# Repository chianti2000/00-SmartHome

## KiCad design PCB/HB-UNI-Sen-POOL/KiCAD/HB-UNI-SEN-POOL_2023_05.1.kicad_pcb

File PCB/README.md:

Dies ist eine Sammplung meiner Platinen für den Bereich HomeMatic, AskSinPP und usw.

## HB-UNI-TEST-PROG-BOARD 

Eine Platine zum Programmieren des ARDUINO PRO MINI und der AVR 328P-AU /1284P-AU sowie für den Frequenztest / Frequenzpairing des Arduino / AVR mit dem CC1101. 

</img>

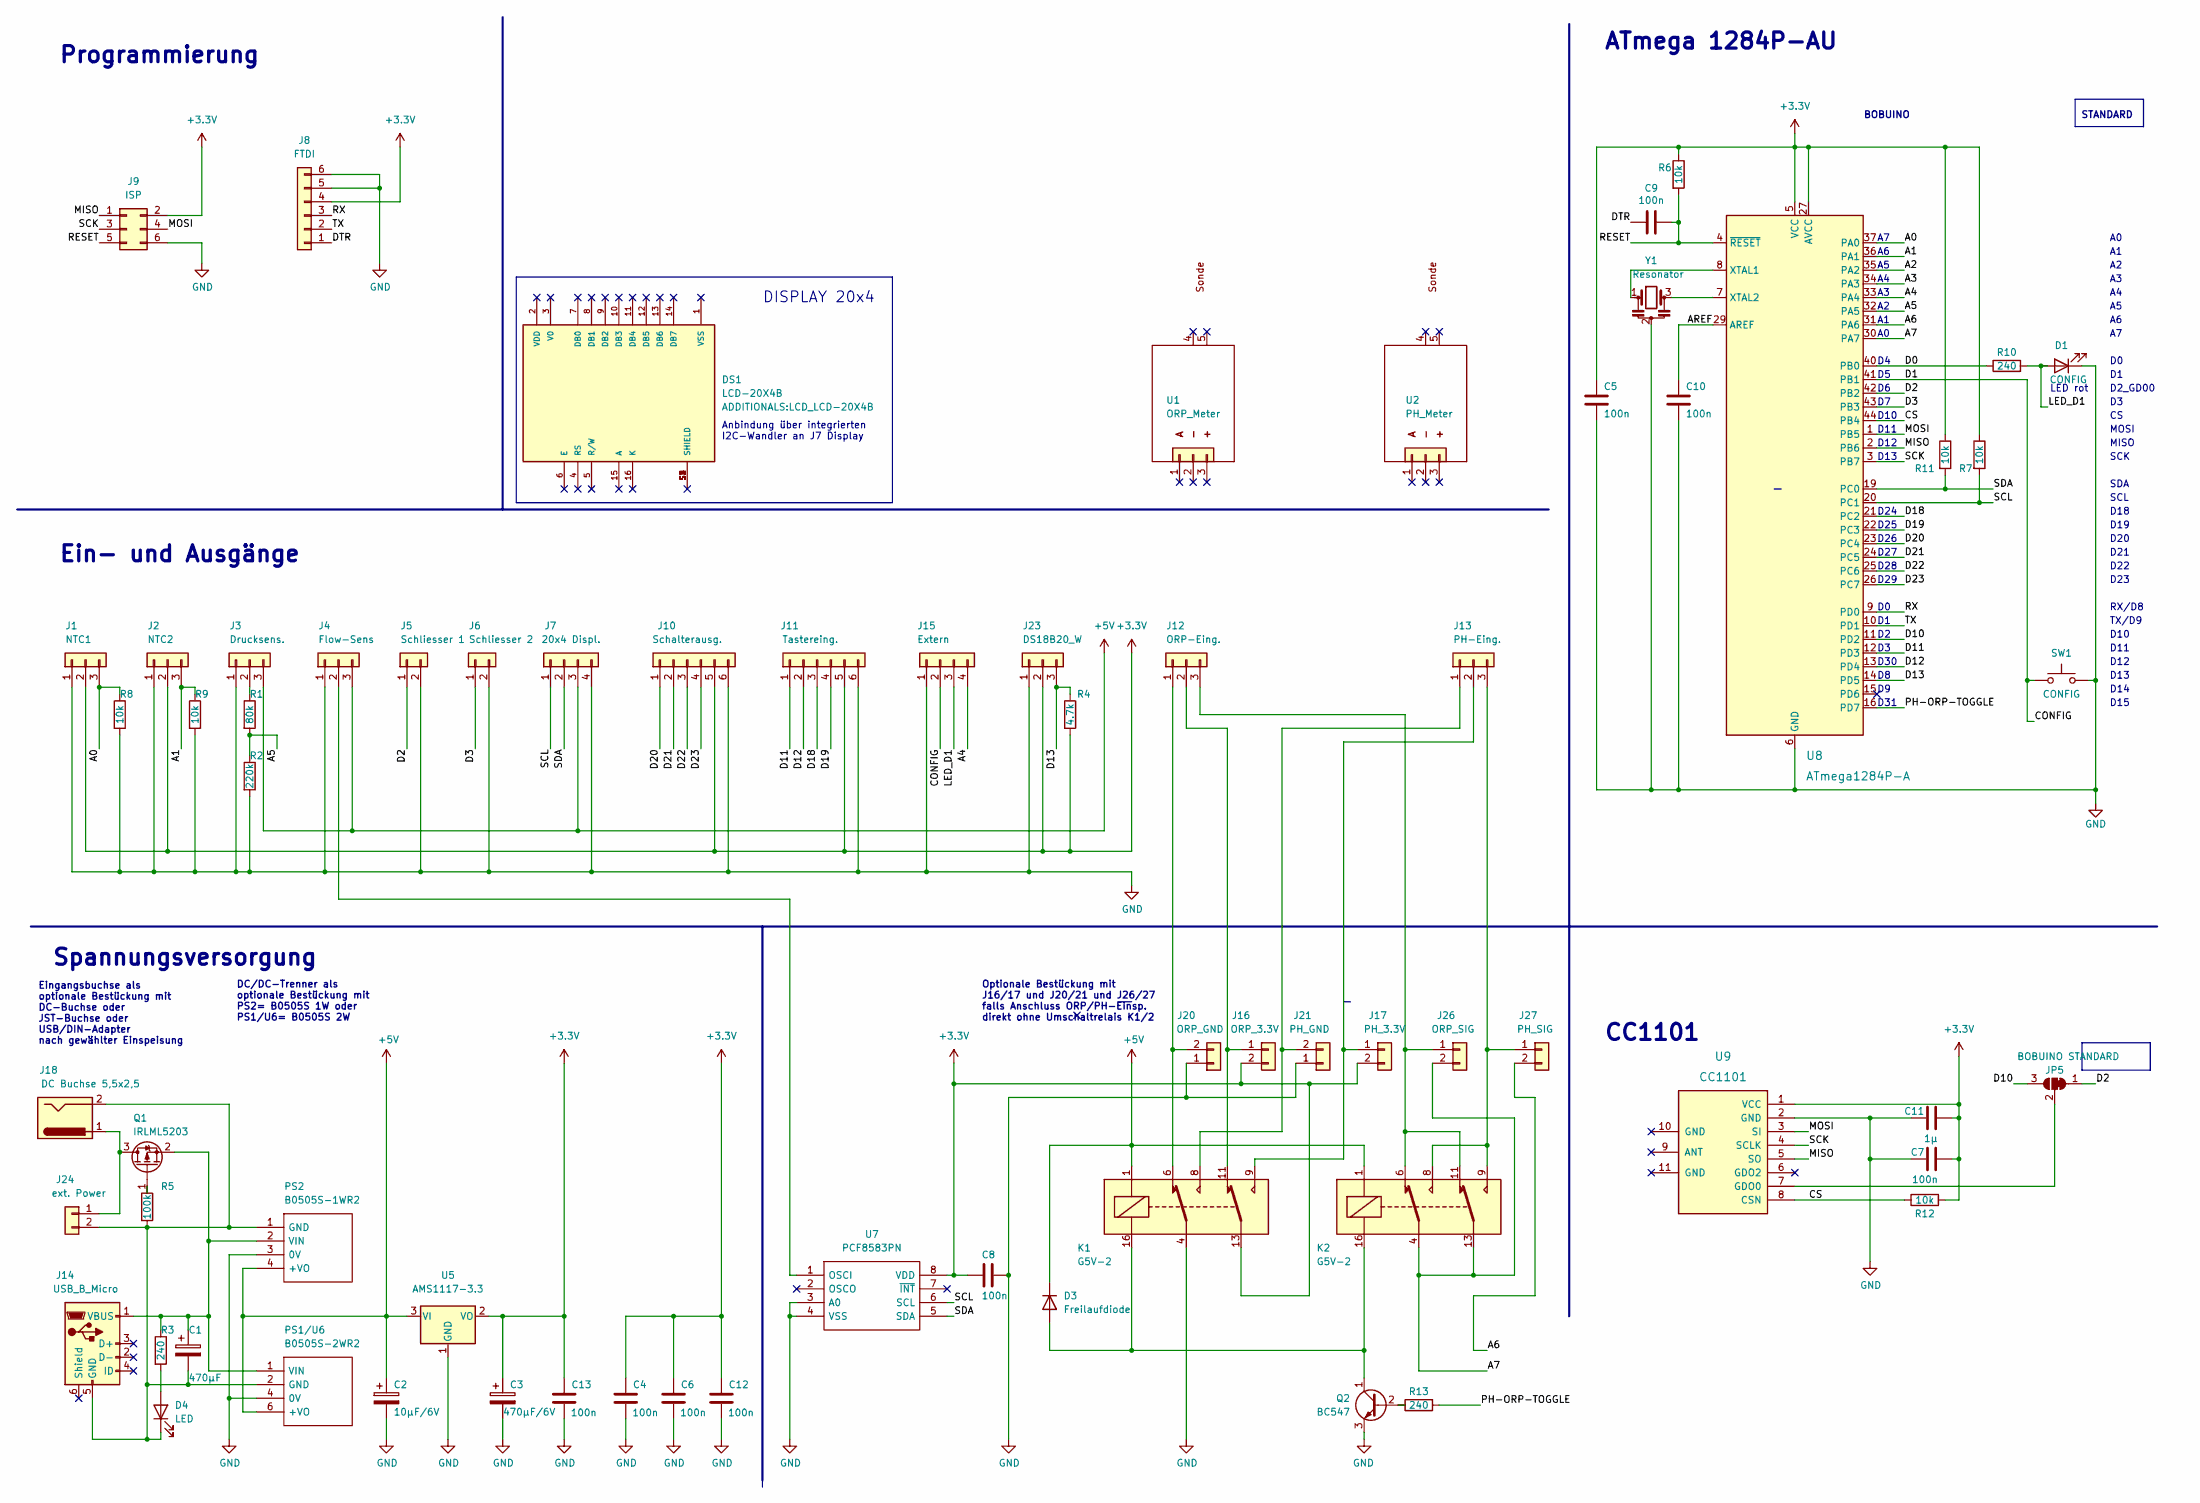
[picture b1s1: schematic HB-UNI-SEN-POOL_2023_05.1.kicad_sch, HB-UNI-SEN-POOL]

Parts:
C1: 470µF; CP_Radial_D5.0mm_P2.50mm
C2: 10µF/6V; CP_Radial_D5.0mm_P2.50mm
C3: 470µF/6V; CP_Radial_D5.0mm_P2.50mm
C4, C5, C6, C7, C8, C9, C10, C12, C13: 100n; C_0805_2012Metric_Pad1.18x1.45mm_HandSolder
C11: 1µ; C_0805_2012Metric_Pad1.18x1.45mm_HandSolder
D1: CONFIG; LED_0805_2012Metric_Pad1.15x1.40mm_HandSolder
D3: Freilaufdiode; D_DO-34_SOD68_P7.62mm_Horizontal
D4: LED; LED_D4.0mm
DS1: LCD-20X4B; LCD_LCD-20X4B; PARTREV N/A
J1: NTC1; TerminalBlock_Phoenix_MPT-0,5-3-2.54_1x03_P2.54mm_Horizontal
J2: NTC2; TerminalBlock_Phoenix_MPT-0,5-3-2.54_1x03_P2.54mm_Horizontal
J3: Drucksens.; TerminalBlock_Phoenix_MPT-0,5-3-2.54_1x03_P2.54mm_Horizontal
J4: Flow-Sens; TerminalBlock_Phoenix_MPT-0,5-3-2.54_1x03_P2.54mm_Horizontal
J5: Schliesser 1; TerminalBlock_Phoenix_MPT-0,5-2-2.54_1x02_P2.54mm_Horizontal
J6: Schliesser 2; TerminalBlock_Phoenix_MPT-0,5-2-2.54_1x02_P2.54mm_Horizontal
J7: 20x4 Displ.; JST_XH_B4B-XH-A_1x04_P2.50mm_Vertical
J8: FTDI; PinSocket_1x06_P2.54mm_Vertical
J9: ISP; PinHeader_2x03_P2.54mm_Vertical
J10: Schalterausg.; TerminalBlock_Phoenix_MPT-0,5-6-2.54_1x06_P2.54mm_Horizontal
J11: Tastereing.; TerminalBlock_Phoenix_MPT-0,5-6-2.54_1x06_P2.54mm_Horizontal
J12: ORP-Eing.; JST_XH_B3B-XH-A_1x03_P2.50mm_Vertical
J13: PH-Eing.; JST_XH_B3B-XH-A_1x03_P2.50mm_Vertical
J14: USB_B_Micro; Micro-USB-auf-DIP-Adapter
J15: Extern; JST_XH_B4B-XH-A_1x04_P2.50mm_Vertical
J16: ORP_3.3V; PinHeader_1x02_P2.54mm_Vertical
J17: PH_3.3V; PinHeader_1x02_P2.54mm_Vertical
J18: DC Buchse 5,5x2,5; BarrelJack_Horizontal
J20: ORP_GND; PinHeader_1x02_P2.54mm_Vertical
J21: PH_GND; PinHeader_1x02_P2.54mm_Vertical
J23: DS18B20_W; TerminalBlock_Phoenix_MPT-0,5-3-2.54_1x03_P2.54mm_Horizontal
J24: ext. Power; TerminalBlock_Phoenix_MPT-0,5-2-2.54_1x02_P2.54mm_Horizontal
J26: ORP_SIG; PinHeader_1x02_P2.54mm_Vertical
J27: PH_SIG; PinHeader_1x02_P2.54mm_Vertical
JP5: BOBUINO STANDARD; SolderJumper-3_P1.3mm_Bridged12_RoundedPad1.0x1.5mm_NumberL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
K1, K2: G5V-2; Relay_DPDT_Omron_G5V-2
PS1/U6: B0505S-2WR2; B0505S2WR2; Manufacturer_Part_Number B0505S-2WR2
PS2: B0505S-1WR2; B0505S1WR2; Manufacturer_Part_Number B0505S-1WR2
Q1: IRLML5203; SOT-23
Q2: BC547; TO-92_Inline
R1: 80k; R_0805_2012Metric_Pad1.20x1.40mm_HandSolder
R2: 220k; R_0805_2012Metric_Pad1.20x1.40mm_HandSolder
R3, R10, R13: 240; R_0805_2012Metric_Pad1.20x1.40mm_HandSolder
R4: 4.7k; R_0805_2012Metric_Pad1.20x1.40mm_HandSolder
R5: 100k; R_0805_2012Metric_Pad1.20x1.40mm_HandSolder
R6, R7, R8, R9, R11, R12: 10k; R_0805_2012Metric_Pad1.20x1.40mm_HandSolder
SW1: CONFIG; SW_SPST_FSMSM
U1: ORP_Meter
U2: PH_Meter
U5: AMS1117-3.3; SOT-223-3_TabPin2
U7: PCF8583PN; DIP802W53P254L950H420Q8N; Manufacturer_Part_Number PCF8583PN; Mouser Part Number N/A
U8: ATmega1284P-A; TQFP-44_10x10mm_P0.8mm
U9: CC1101
Y1: Resonator; Resonator_SMD_muRata_CSTCC-3pin_7.2x3.0mm_HandSoldering

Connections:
+3.3V: C3.1, C4.1, C5.1, C6.1, C7.2, C8.2, C11.2, C12.1, C13.1, J1.2, J2.2, J8.4, J9.2, J10.5, J11.5, J16.2, J17.2, J23.2, K1.13, R4.2, R6.1, R7.1, R11.1, R12.2, U5.2 (VO), U7.8 (VDD), U8.5 (VCC), U8.17 (VCC), U8.27 (AVCC), U8.38 (VCC), U9.1 (VCC)
+5V: C2.1, D3.1 (K), J3.3, J4.3, J7.3, K1.1, K2.1, PS1/U6.6 (+VO), PS2.4 (+VO), U5.3 (VI)
/A0: J1.3, R8.1, U8.37 (PA0)
/A1: J2.3, R9.1, U8.36 (PA1)
/A2: U8.35 (PA2)
/A3: U8.34 (PA3)
/A4: J15.4, U8.33 (PA4)
/A5: R1.2, R2.1, U8.32 (PA5)
/A6: J27.2, U8.31 (PA6)
/A7: J26.2, K2.4, K2.13, U8.30 (PA7)
/AREF: C10.1, U8.29 (AREF)
/CONFIG: J15.2, SW1.1, U8.41 (PB1)
/CS: R12.1, U8.44 (PB4), U9.8 (CSN)
/D0: R10.1, U8.40 (PB0)
/D2: J5.1, JP5.1 (A), U8.42 (PB2)
/D3: J6.1, U8.43 (PB3)
/D10: JP5.3 (B), U8.11 (PD2)
/D11: J11.1, U8.12 (PD3)
/D12: J11.2, U8.13 (PD4)
/D13: J23.3, R4.1, U8.14 (PD5)
/D18: J11.3, U8.21 (PC2)
/D19: J11.4, U8.22 (PC3)
/D20: J10.1, U8.23 (PC4)
/D21: J10.2, U8.24 (PC5)
/D22: J10.3, U8.25 (PC6)
/D23: J10.4, U8.26 (PC7)
/DTR: C9.1, J8.1
/LED_D1: D1.2 (A), J15.3, R10.2
/MISO: J9.1, U8.2 (PB6), U9.5 (SO)
/MOSI: J9.4, U8.1 (PB5), U9.3 (SI)
/PH-ORP-TOGGLE: R13.2, U8.16 (PD7)
/RESET: C9.2, J9.5, R6.2, U8.4 (~RESET)
/RX: J8.3, U8.9 (PD0)
/SCK: J9.3, U8.3 (PB7), U9.4 (SCLK)
/SCL: J7.1, R7.2, U7.6 (SCL), U8.20 (PC1)
/SDA: J7.2, R11.2, U7.5 (SDA), U8.19 (PC0)
/TX: J8.2, U8.10 (PD1)
GND: C2.2, C3.2, C4.2, C5.2, C6.2, C7.1, C8.1, C10.2, C11.1, C12.2, C13.2, D1.1 (K), J1.1, J2.1, J3.1, J4.1, J5.2, J6.2, J7.4, J8.5, J8.6, J9.6, J10.6, J11.6, J15.1, J20.1, J21.1, J23.1, K1.4, PS1/U6.4 (0V), PS2.3 (0V), Q2.3 (E), R2.2, R8.2, R9.2, SW1.2, U5.1 (GND), U7.3 (A0), U7.4 (VSS), U8.6 (GND), U8.18 (GND), U8.28 (GND), U8.39 (GND), U9.2 (GND), Y1.2
unnamed: C1.1, J14.1 (VBUS), PS1/U6.1 (VIN), PS2.2 (VIN), Q1.2 (S), R3.1
unnamed: C1.2, D4.1 (K), J14.5 (GND), J18.2, J24.2, PS1/U6.2 (GND), PS2.1 (GND), R5.2
unnamed: D3.2 (A), K1.16, K2.16, Q2.1 (C)
unnamed: D4.2 (A), R3.2
unnamed: J3.2, R1.1
unnamed: J4.2, U7.1 (OSCI)
unnamed: J12.1, J20.2, K1.6
unnamed: J12.2, J16.1, K1.11
unnamed: J12.3, J26.1, K2.6, K2.11
unnamed: J13.1, J21.2, K1.8
unnamed: J13.2, J17.1, K1.9
unnamed: J13.3, J27.1, K2.8, K2.9
unnamed: J18.1, J24.1, Q1.3 (D)
unnamed: JP5.2 (C), U9.7 (GDO0)
unnamed: Q1.1 (G), R5.1
unnamed: Q2.2 (B), R13.1
unnamed: U8.7 (XTAL2), Y1.3
unnamed: U8.8 (XTAL1), Y1.1

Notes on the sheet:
DC/DC-Trenner als optionale Bestückung mit PS2= B0505S 1W oder PS1/U6= B0505S 2W
Ein- und Ausgänge
SCK
D23
D30
D19
D22
RX/D8
Eingangsbuchse als optionale Bestückung mit DC-Buchse oder JST-Buchse oder USB/DIN-Adapter nach gewählter Einspeisung
D13
D15
D11
D14
SDA
MISO
DISPLAY 20x4
D26
D29
Optionale Bestückung mit J16/17 und J20/21 und J26/27 falls Anschluss ORP/PH-Einsp. direkt ohne Umschaltrelais K1/2
LED rot
CC1101
D10
D18
SCL
D2_GD00
TX/D9
Spannungsversorgung
D12
D24
ATmega 1284P-AU
Anbindung über integrierten I2C-Wandler an J7 Display
Programmierung
BOBUINO STANDARD
D25
D31
D28
D21
MOSI
D27
D20

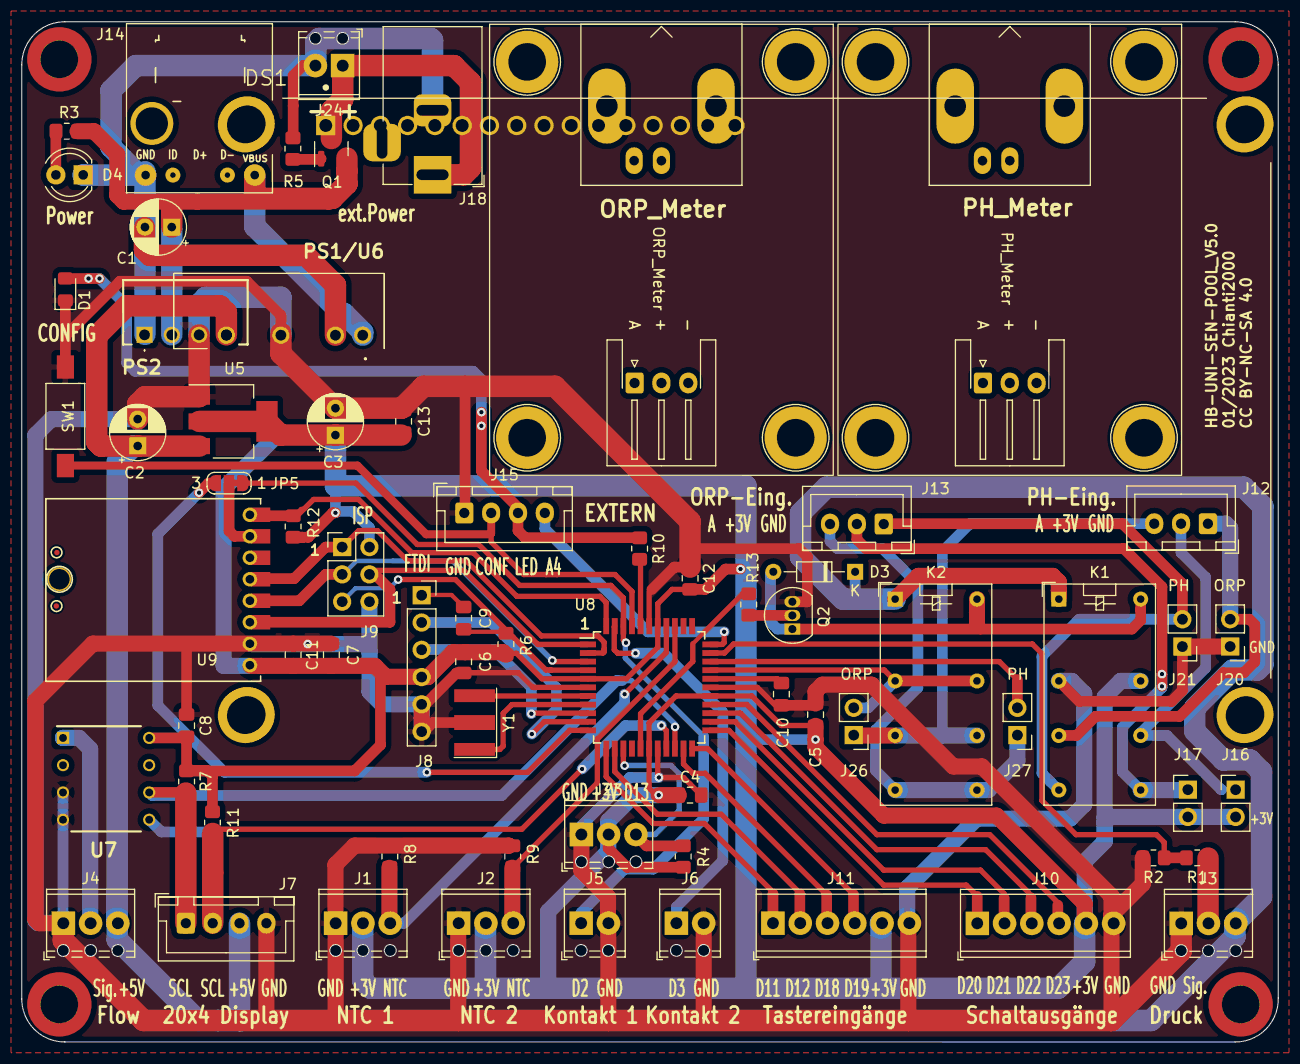
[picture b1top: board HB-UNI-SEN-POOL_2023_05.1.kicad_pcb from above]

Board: 2 copper layers, 117.0 x 95.0 mm, 77 parts (0 on the bottom side), 54 nets.

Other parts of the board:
REF2, REF3, REF4, REF21: MountingHole_3.4mm_Pad_TopBottom_MOD; MountingHole_3.4mm_Pad_TopBottom
REF11, REF12, REF13, REF14: MountingHole_3.5mm_Pad_TopBottom

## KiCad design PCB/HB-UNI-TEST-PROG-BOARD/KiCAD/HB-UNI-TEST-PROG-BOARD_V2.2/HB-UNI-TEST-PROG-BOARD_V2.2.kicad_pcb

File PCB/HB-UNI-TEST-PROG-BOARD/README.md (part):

# HB-UNI-TEST-PROG-BOARD 

Eine Platine zum Programmieren des ARDUINO PRO MINI und der AVR 328P-AU /1284P-AU sowie für den Frequenztest /Frequenzpairing der programmierten AVR mit dem CC1101 Funkmodul. 

Ich möchte hier mein Programmier- und Testboard für den Arduino Pro Mini, 328P-AU und 1284P-AU und kompatible mit TQFP-32 und -44 Sockel vorstellen.
Ausgangspunkt war die HB-CC01-Testbench von Tom. Da aber immer mehr User AVR-Chips bei ihren Selbstbauprojekten einsetzen, ist sicher auch hier der Bedarf für eine Programmier- und Testbench vorhanden. 

## HB-UNI-TEST-PROG-BOARD_V1.2

Im ersten Schritt bestand die folgende Zielsetzung bezüglich der Funktionalität:

- [ ] Programmierboard für 328P-AU bzw. 1284P-AU und kompatible. Der Anschluss über ISP bzw. FTDI ist möglich.

- [ ] Testboard für den Frequenztest /Frequenzkorrektur des CC1101 in Verbindung mit 328P-AU bzw. 1284P-AU, so daß der CC1101 mit dem angepassten AVR-Chip später direkt gemeinsam "verbaut" werden kann.

- [ ] Weiterentwicklung der "Testklemme" mit POGO-Pins von Toms Testbench  https://github.com/TomMajor/SmartHome/tree/master/HB-CC1101-Testbench zur Testklammer zum schnelleren /einfacheren CC1101 Tausch. Herausführen des GDO2-Pins als Möglichkeit für den Anschluss eines Oszillators.

- [ ] Spannungsversorgung über Batteriezelle AA und Wandler auf 3,3 V oder USB-Anschluss mit Spannungsregler 3,3V. Der USB Buchsen Typ kann über ein aufgelötetes USB-DIP Board nach eigenen Wünschen gewählt werden. Vorwahl der Einspeisung über Jumper, hier kann bei Bedarf auch der Gesamtstrom gemessen werden. Das CLOCK-Signal kann über den Jumper CLOCKSEL deaktiviert werden um die Strommessung nicht zu verfälschen.

- [ ] Möglichkeit der Strommessung getrennt für Gesamtstrom (I-BAT bzw. I.EXT), I-328P-AU,            I-1284P-AU, I-CC1101 und I-I2C. Die Shunt- Widerstände können bei Bedarf bestückt oder weggelassen werden.

- [ ] Funktions- bzw. Programmtest der Schaltung der AVR-Chip sowie Messung der Stromaufnahme im "Real-Betrieb" über:
  - den am vorgesehenen I2C-Anschluss angeschlossenen Messmodulen (Strommessung      I-I2C bei Bedarf über Jumperklemme möglich).
  - Anschluss von Bauteilen bzw. eines Breadboard an den 1:1 auf die Buchsenleisten herausgeführten Anschlüssen der AVR-Chips .

Der Sockel für den 1284P-AU wurde entsprechend dem BOBUINO-Pinout beschriftet und verschaltet. Die Umstellung Bobuino- auf Standard-Pinout für die Ansteuerung GD00-PIN des CC1101 ist über einen Jumper vorgesehen. Somit können auch Programme mit Standard-Pinout im Zusammenspiel mit dem CC1101 getestet werden. Im Programm ist nur der PIN für die CONFIG-LED  anzupassen.

Für den Frequenztest mit Standard-Pinout ist trotzdem ein anderer Sketch als für den "klassischen" Test mit Bobuino-Pinout notwendig. Ich habe beide Varianten unter FILES abgelegt.  

### Bilder
</img>

### Schemata / Gerber-File
[:arrow_right: Schemata HB-UNI-TEST-PROG-BOARD_V1.2](FILES/Schema_HB-UNI-TEST-PROG-BOARD_V1.2.pdf)
[:arrow_right: Gerber HB-UNI-TEST-PROG-BOARD_V1.2](GERBER/HB-UNI-TEST-PROG-BOARD_V1.2.rar)

## HB-UNI-TEST-PROG-BOARD_V2.2

In einer zweiten Variante wurde das  HB-UNI-TEST-PROG-BOARD um eine Testbench für den Arduino Pro Mini mit den o.g. Funktionalitäten erweitert.

Der Arduino Pro Mini kann sowohl über den FTDI-Adapter als auch über den ISP programmiert werden. Im Fall des ISP ist ein setzen der FUSES und aufspielen eines neuen Bootloaders des Arduino Pro Mini möglich.

Als Nebeneffekt kann über den verbauten FTDI-Adapter direkt auf den FTDI-Anschluss des Boards zum Hochladen bzw. als serieller Monitor zugegriffen werden. Wenn man den Arduino Pro Mini als ISP programmiert, kann er als ISP-Programmer für die AVR-Chips auf den Sockel genutzt werden.

### Bilder
</img></img></img>

### Schemata / Gerber-File
[:arrow_right: Schemata HB-UNI-TEST-PROG-BOARD_V2.2](FILES/Schema_HB-UNI-TEST-PROG-BOARD_V2.2.pdf)
[:arrow_right: Gerber HB-UNI-TEST-PROG-BOARD_V2.2](GERBER/HB-UNI-TEST-PROG-BOARD_V2.2.rar)

### Funktionen
Über DIP-Schalter lassen sich die gewünschten Funktionen des Boards gemäß dieser Tabellen einstellen.

</img>
</img>

[:arrow_right: PROGRAMMIERUNG UND FREQUENZPAIRING AVR-CHIP (328P-AU/1284P-AU) AUF TQFP-32 oder -44 Sockel](FILES/HB-UNI-TEST-PROG-BOARD_Funktionswahlschalter_1.pdf)

[:arrow_right: PROGRAMMIERUNG UND FREQUENZPAIRING ARDUINO PRO NANO AUF 24 +4 POLIGEM SOCKEL](FILES/HB-UNI-TEST-PROG-BOARD_Funktionswahlschalter_2.pdf)

## Testklammer für CC1101

Als Weiterentwicklung und Anpassung der Testklemme von Toms Testbench (https://github.com/TomMajor/SmartHome/tree/master/HB-CC1101-Testbench) sowie von Patricks HM-Sensor Programmierklemme (https://www.thingiverse.com/thing:4564797) ist zum schnelleren Wechsel des CC1101 diese Testklammer entstanden.

Man benötigt neben den 3D-Druckteilen:

- 1x  Druckfeder 9.5x19mm
- 11x Pogo-pin 1,3mm Konische Kopf 1,0mm Fingerhut Für Elektrowerkzeug P75-E2 (z.B. von hier https://de.aliexpress.com/item/32874022638.html?spm=a2g0s.9042311.0.0.27424c4dGXI81E)
- 1x  M3 Mutter
- 1x  M3x12mm Schraube

Die Löcher für die Pogos müssen ggf. nachgebohrt werden. Den Antennendraht habe ich auf 72 mm Länge geschnitten, da der Pogo-Pin ca. 14 mm lang ist und schon als Antenne wirkt (72mm + 14mm = 86 mm).

Auf den nachfolgenden Bildern ist der Zusammenbau gut zu erkennen. 

### Bilder
</img></img></img>

Die Dummyplatte wird nach dem Einstecken der Pogo-Stifte Oben aufgesteckt (das geht mit Absicht etwas straff). Sie arretiert die Stifte auf die richtige Länge.Auf der Lötseite sollten diese dann ca. 2mm herausschauen. Nach dem verlöten der Pogo-Stifte kann sie wieder entfernt werden.

</img></img></img>

</img></img></img>

</img></img>

### Stückliste
| STÜCKLISTE |                           |                                |                                 |                                      |
| ---------- | ------------------------- | ------------------------------ | ------------------------------- | ------------------------------------ |
|            |                           |                                |                                 |                                      |
| Anzahl     | Name                      | Wert                           | Gehäuse                         | Bemerkung                            |
|            | BT1                       | Batteriehalter AA              |                                 | KEYSTONE 1028 oder GOOBAY_AA         |
|            | C1, C3                    | 100µF/mind. 5V                 | bedrahtet, Radial               |                                      |
|            | C5  - C12, C14 - C15, C18 | 100n                           | 0805                            |                                      |
|            | C13                       | 1µ                             | 0805                            |                                      |
|            | C2, C4, C17               | 10µF / mind. 5V                | 0805                            |                                      |
|            | R1, R2, R3, R6-R8,  R20   | 10k                            | 0805                            |                                      |
|            | R9                        | 100k                           | 0805                            |                                      |
|            | R4, R5,R10, R18           | 1,5k                           | 0805                            |                                      |
|            | R11 - R19                 | SHUNT                          | 0805                            | bei Bedarf bestücken                 |
|            | D1                        | CLOCK                          | 0805                            | LED grün                             |
|            | D2 - D4                   | CONFIG                         | 0805                            | LED rot                              |
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
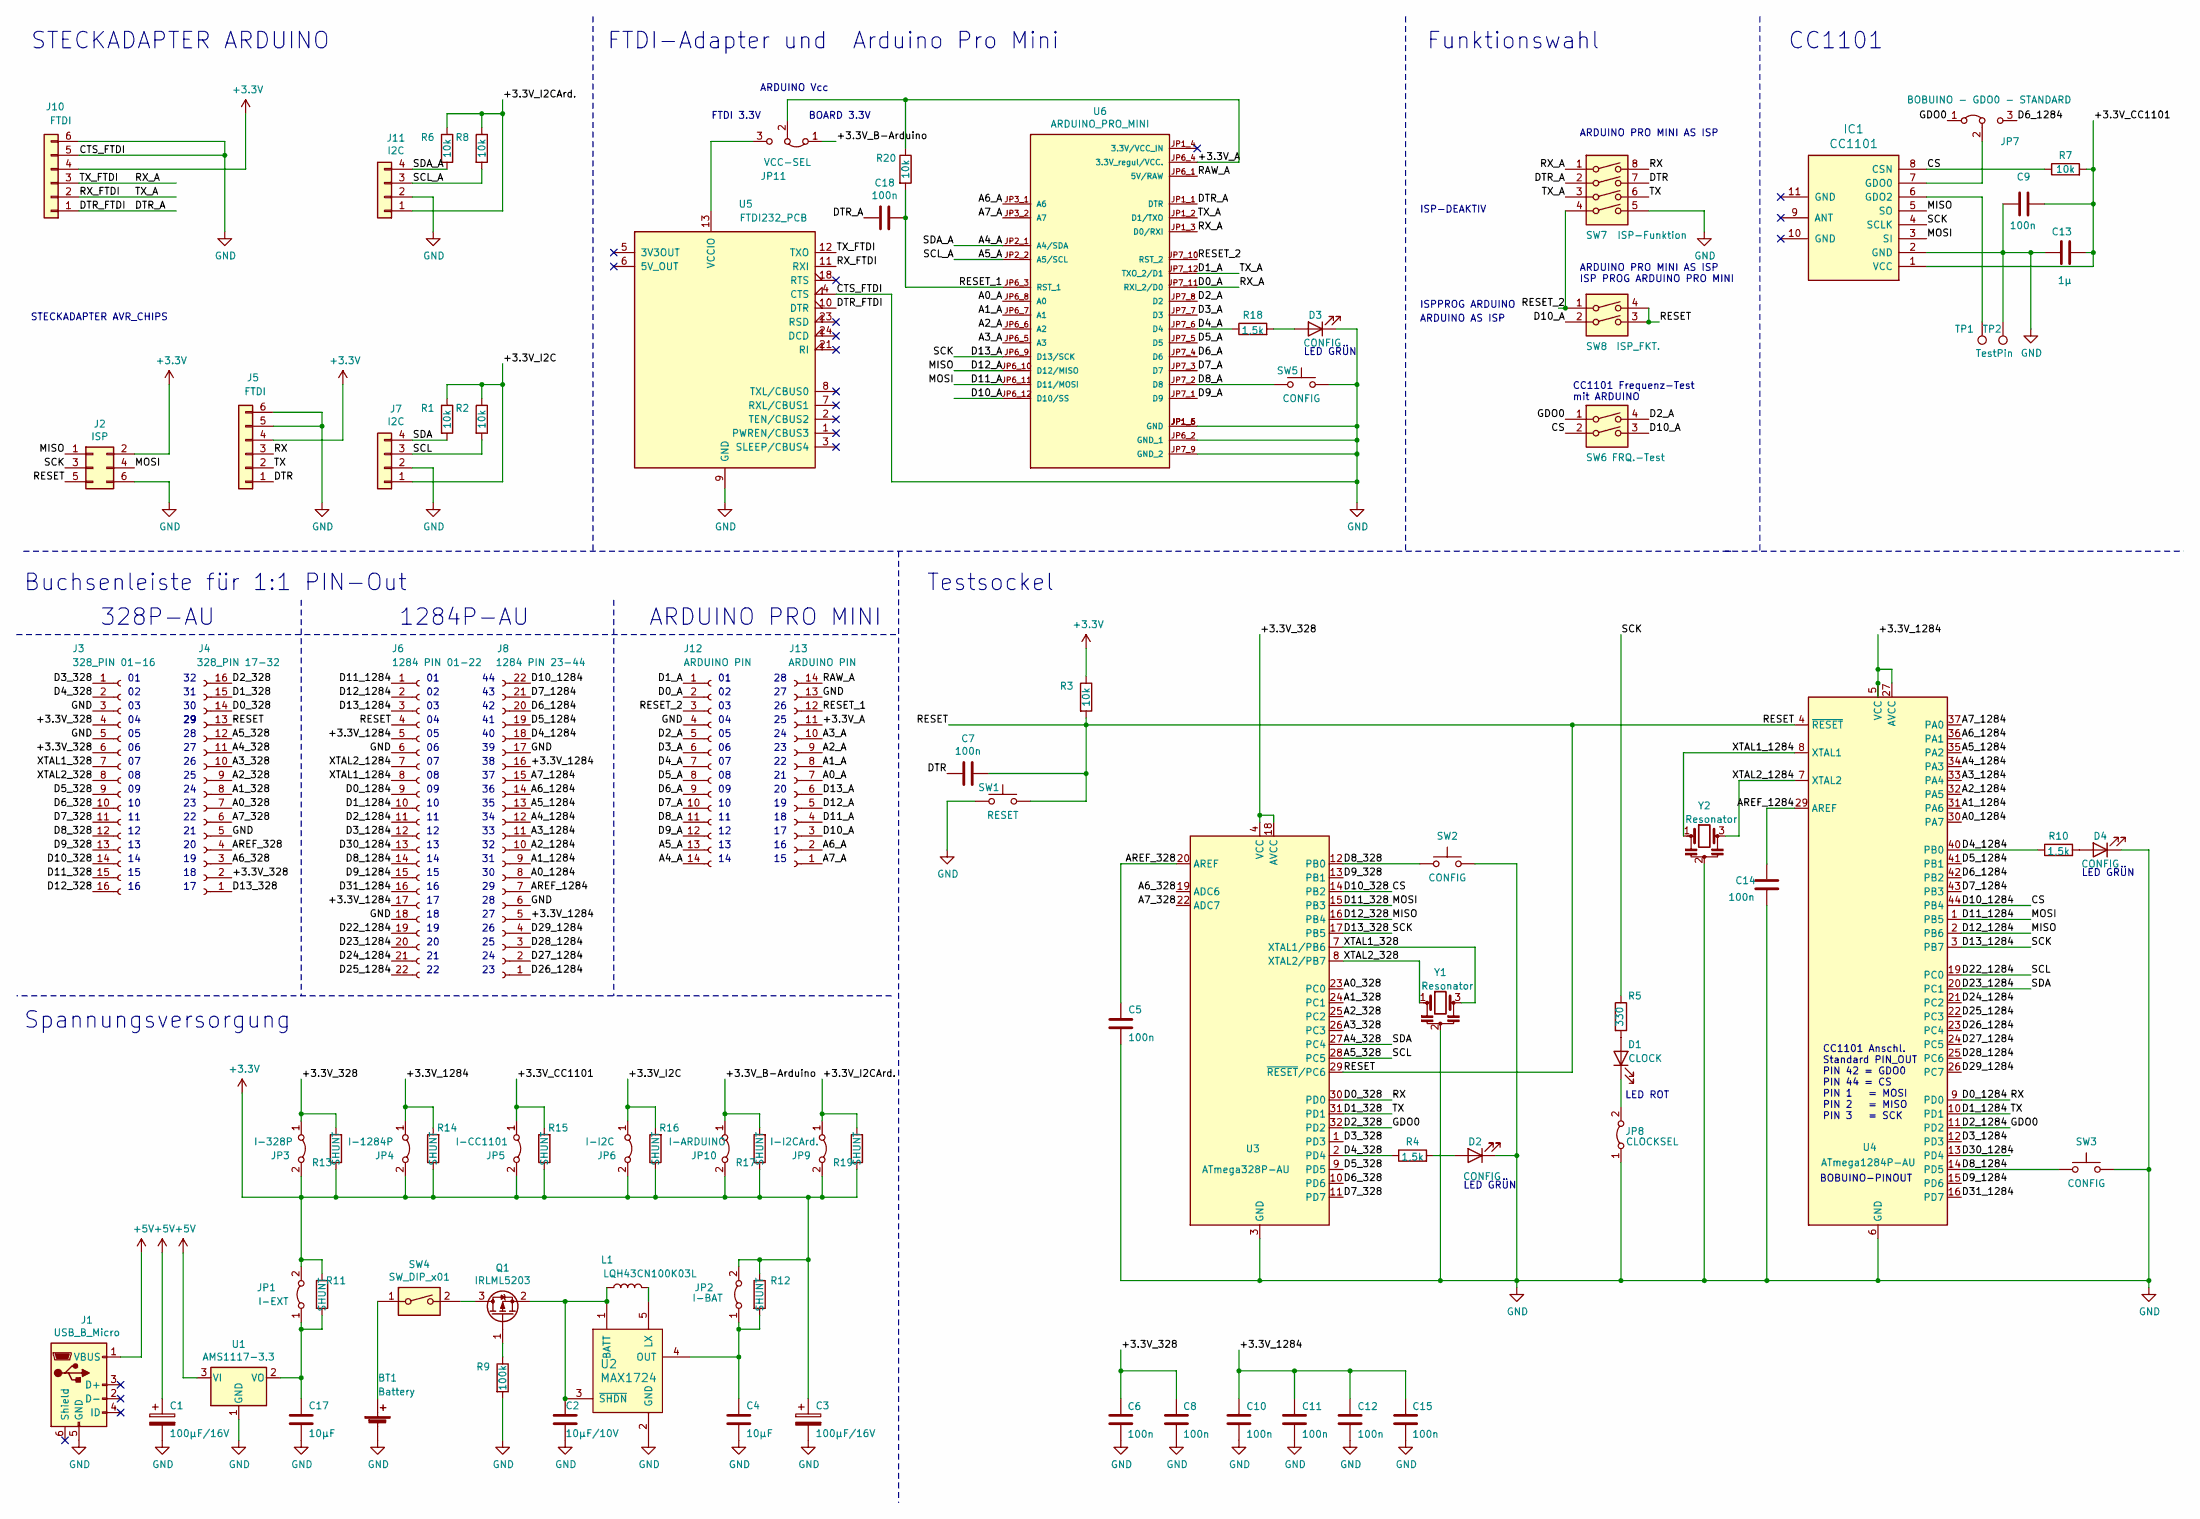
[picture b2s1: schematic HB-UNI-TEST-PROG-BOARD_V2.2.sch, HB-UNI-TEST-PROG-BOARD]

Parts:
BT1: Battery; BATTERY_HOLDER_GOOBAY_AA
C1, C3: 100µF/16V; CP_Radial_D7.5mm_P2.50mm
C2: 10µF/10V; C_0805_2012Metric_Pad1.15x1.40mm_HandSolder
C4, C17: 10µF; C_0805_2012Metric_Pad1.15x1.40mm_HandSolder
C5, C6, C7, C8, C9, C10, C11, C12, C14, C15, C18: 100n; C_0805_2012Metric_Pad1.15x1.40mm_HandSolder
C13: 1µ; C_0805_2012Metric_Pad1.15x1.40mm_HandSolder
D1: CLOCK; LED_0805_2012Metric_Pad1.15x1.40mm_HandSolder
D2, D3, D4: CONFIG; LED_0805_2012Metric_Pad1.15x1.40mm_HandSolder
IC1: CC1101; CC1101_POGOPIN
J1: USB_B_Micro; USB-MICRO-DIP
J2: ISP; PinHeader_2x03_P2.54mm_Vertical
J3: 328_PIN 01-16; PinSocket_1x16_P2.54mm_Vertical
J4: 328_PIN 17-32; PinSocket_1x16_P2.54mm_Vertical
J5, J10: FTDI; PinSocket_1x06_P2.54mm_Vertical
J6: 1284 PIN 01-22; PinSocket_1x22_P2.54mm_Vertical
J7, J11: I2C; PinSocket_1x04_P2.54mm_Vertical
J8: 1284 PIN 23-44; PinSocket_1x22_P2.54mm_Vertical
J12, J13: ARDUINO PIN; PinSocket_1x14_P2.54mm_Vertical
JP1: I-EXT; PinHeader_1x02_P2.54mm_Vertical
JP2: I-BAT; PinHeader_1x02_P2.54mm_Vertical
JP3: I-328P; PinHeader_1x02_P2.54mm_Vertical
JP4: I-1284P; PinHeader_1x02_P2.54mm_Vertical
JP5: I-CC1101; PinHeader_1x02_P2.54mm_Vertical
JP6: I-I2C; PinHeader_1x02_P2.54mm_Vertical
JP7: BOBUINO - GDO0 - STANDARD; PinHeader_1x03_P2.54mm_Vertical
JP8: CLOCKSEL; PinHeader_1x02_P2.54mm_Vertical
JP9: I-I2CArd.; PinHeader_1x02_P2.54mm_Vertical
JP10: I-ARDUINO; PinHeader_1x02_P2.54mm_Vertical
JP11: VCC-SEL; PinHeader_1x03_P2.54mm_Vertical
L1: LQH43CN100K03L; L_1812_4532Metric_Pad1.30x3.40mm_HandSolder
Q1: IRLML5203; SOT-23_Handsoldering
R1, R2, R3, R6, R7, R8, R20: 10k; R_0805_2012Metric_Pad1.15x1.40mm_HandSolder
R4, R10, R18: 1,5k; R_0805_2012Metric_Pad1.15x1.40mm_HandSolder
R5: 330; R_0805_2012Metric_Pad1.15x1.40mm_HandSolder
R9: 100k; R_0805_2012Metric_Pad1.15x1.40mm_HandSolder
R11, R12, R13, R14, R15, R16, R17, R19: SHUNT; R_0805_2012Metric_Pad1.15x1.40mm_HandSolder
SW1: RESET; SW_SPST_FSMSM
SW2, SW3, SW5: CONFIG; SW_SPST_FSMSM
SW4: SW_DIP_x01; SW_DIP_SPSTx01_Slide_9.78x4.72mm_W7.62mm_P2.54mm
SW6: FRQ.-Test; SW_DIP_SPSTx02_Slide_9.78x7.26mm_W7.62mm_P2.54mm
SW7: ISP-Funktion; SW_DIP_SPSTx04_Slide_9.78x12.34mm_W7.62mm_P2.54mm
SW8: ISP_FKT.; SW_DIP_SPSTx02_Slide_9.78x7.26mm_W7.62mm_P2.54mm
TP1, TP2: TestPin; PinSocket_1x01_P2.54mm_Vertical
U1: AMS1117-3.3; SOT-223
U2: MAX1724; SOT-23-5_HandSoldering
U3: ATmega328P-AU; DIP-32_W15.24mm_Socket
U4: ATmega1284P-AU; DIP-48_W15.24mm_Socket
U5: FTDI232_PCB
U6: ARDUINO_PRO_MINI; MODULE_ARDUINO_PRO_MINI; PARTREV N/A
Y1, Y2: Resonator; Resonator_SMD-3Pin_7.2x3.0mm

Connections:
+3V3: C3.1, J2.2, J5.4, J10.4, JP1.2 (B), JP2.2 (B), JP3.2 (B), JP4.2 (B), JP5.2 (B), JP6.2 (B), JP9.2 (B), JP10.2 (B), R3.1, R11.1, R12.1, R13.1, R14.1, R15.1, R16.1, R17.1, R19.1
+5V: C1.1, J1.1 (VBUS), U1.3 (VI)
/+3.3V_328: C6.1, C8.1, J3.4, J3.6, J4.2, JP3.1 (A), R13.2, U3.4 (VCC), U3.6 (VCC), U3.18 (AVCC)
/+3.3V_1284: C10.1, C11.1, C12.1, C15.1, J6.5, J6.17, J8.5, J8.16, JP4.1 (A), R14.2, U4.5 (VCC), U4.17 (VCC), U4.27 (AVCC), U4.38 (VCC)
/+3.3V_A: J13.11, JP11.2 (C), R20.1, U6.JP6_4 (3.3V_regul/VCC.)
/+3.3V_B-Arduino: JP10.1 (A), JP11.1 (A), R17.2
/+3.3V_CC1101: C9.1, C13.2, IC1.1 (VCC), JP5.1 (A), R7.2, R15.2
/+3.3V_I2C: J7.1, JP6.1 (A), R1.1, R2.1, R16.2
/+3.3V_I2CArd.: J11.1, JP9.1 (A), R6.1, R8.1, R19.2
/A0_328: J4.7, U3.23 (PC0)
/A0_1284: J8.8, U4.30 (PA7)
/A0_A: J13.7, U6.JP6_8 (A0)
/A1_328: J4.8, U3.24 (PC1)
/A1_1284: J8.9, U4.31 (PA6)
/A1_A: J13.8, U6.JP6_7 (A1)
/A2_328: J4.9, U3.25 (PC2)
/A2_1284: J8.10, U4.32 (PA5)
/A2_A: J13.9, U6.JP6_6 (A2)
/A3_328: J4.10, U3.26 (PC3)
/A3_1284: J8.11, U4.33 (PA4)
/A3_A: J13.10, U6.JP6_5 (A3)
/A4_328: J4.11, J6.20, J7.4, R1.2, U3.27 (PC4), U4.20 (PC1)
/A4_1284: J8.12, U4.34 (PA3)
/A4_A: J11.4, J12.14, R6.2, U6.JP2_1 (A4/SDA)
/A5_328: J4.12, J6.19, J7.3, R2.2, U3.28 (PC5), U4.19 (PC0)
/A5_1284: J8.13, U4.35 (PA2)
/A5_A: J11.3, J12.13, R8.2, U6.JP2_2 (A5/SCL)
/A6_328: J4.3, U3.19 (ADC6)
/A6_1284: J8.14, U4.36 (PA1)
/A6_A: J13.2, U6.JP3_1 (A6)
/A7_328: J4.6, U3.22 (ADC7)
/A7_1284: J8.15, U4.37 (PA0)
/A7_A: J13.1, U6.JP3_2 (A7)
/AREF_328: C5.1, J4.4, U3.20 (AREF)
/AREF_1284: C14.1, J8.7, U4.29 (AREF)
/CS: IC1.8 (CSN), J3.14, J8.22, R7.1, SW6.2, U3.14 (PB2), U4.44 (PB4)
/D0_1284: J4.14, J5.3, J6.9, SW7.8, U3.30 (PD0), U4.9 (PD0)
/D0_A: J10.3, J12.2, SW7.1, U5.12 (TXO), U6.JP1_3 (D0/RXI), U6.JP7_11 (RXI_2/D0)
/D1_1284: J4.15, J5.2, J6.10, SW7.6, U3.31 (PD1), U4.10 (PD1)
/D1_A: J10.2, J12.1, SW7.3, U5.11 (RXI), U6.JP1_2 (D1/TXO), U6.JP7_12 (TXO_2/D1)
/D2_1284: J4.16, J6.11, JP7.1 (A), SW6.1, U3.32 (PD2), U4.11 (PD2)
/D2_A: J12.5, SW6.4, U6.JP7_8 (D2)
/D3_328: J3.1, U3.1 (PD3)
/D3_1284: J6.12, U4.12 (PD3)
/D3_A: J12.6, U6.JP7_7 (D3)
/D4_328: J3.2, R4.1, U3.2 (PD4)
/D4_1284: J8.18, R10.1, U4.40 (PB0)
/D4_A: J12.7, R18.1, U6.JP7_6 (D4)
/D5_328: J3.9, U3.9 (PD5)
/D5_1284: J8.19, U4.41 (PB1)
/D5_A: J12.8, U6.JP7_5 (D5)
/D6_328: J3.10, U3.10 (PD6)
/D6_1284: J8.20, JP7.3 (B), U4.42 (PB2)
/D6_A: J12.9, U6.JP7_4 (D6)
/D7_328: J3.11, U3.11 (PD7)
/D7_1284: J8.21, U4.43 (PB3)
/D7_A: J12.10, U6.JP7_3 (D7)
/D8_328: J3.12, SW2.1, U3.12 (PB0)
/D8_1284: J6.14, SW3.1, U4.14 (PD5)
/D8_A: J12.11, SW5.1, U6.JP7_2 (D8)
/D9_328: J3.13, U3.13 (PB1)
/D9_1284: J6.15, U4.15 (PD6)
/D9_A: J12.12, U6.JP7_1 (D9)
/D10_A: J13.3, SW6.3, SW8.2, U6.JP6_12 (D10/SS)
/D11_1284: IC1.3 (SI), J2.4, J3.15, J6.1, J13.4, U3.15 (PB3), U4.1 (PB5), U6.JP6_11 (D11/MOSI)
/D12_1284: IC1.5 (SO), J2.1, J3.16, J6.2, J13.5, U3.16 (PB4), U4.2 (PB6), U6.JP6_10 (D12/MISO)
/D13_1284: IC1.4 (SCLK), J2.3, J4.1, J6.3, J13.6, R5.1, U3.17 (PB5), U4.3 (PB7), U6.JP6_9 (D13/SCK)
/D24_1284: J6.21, U4.21 (PC2)
/D25_1284: J6.22, U4.22 (PC3)
/D26_1284: J8.1, U4.23 (PC4)
/D27_1284: J8.2, U4.24 (PC5)
/D28_1284: J8.3, U4.25 (PC6)
/D29_1284: J8.4, U4.26 (PC7)
/D30_1284: J6.13, U4.13 (PD4)
/D31_1284: J6.16, U4.16 (PD7)
/DTR: C7.2, J5.1, SW7.7
/DTR_A: C18.2, J10.1, SW7.2, U5.10 (DTR), U6.JP1_1 (DTR)
/RAW_A: J13.14, U6.JP6_1 (5V/RAW)
/RESET: C7.1, J2.5, J4.13, J6.4, R3.2, SW1.1, SW8.3, SW8.4, U3.29 (~RESET~/PC6), U4.4 (~RESET)
/RESET_1: C18.1, J13.12, R20.2, U6.JP6_3 (RST_1)
/RESET_2: J12.3, SW7.4, SW8.1, U6.JP7_10 (RST_2)
/XTAL1_328: J3.7, U3.7 (XTAL1/PB6), Y1.3
/XTAL1_1284: J6.8, U4.8 (XTAL1), Y2.1
/XTAL2_328: J3.8, U3.8 (XTAL2/PB7), Y1.1
/XTAL2_1284: J6.7, U4.7 (XTAL2), Y2.3
GND: BT1.2 (-), C1.2, C2.2, C3.2, C4.2, C5.2, C6.2, C8.2, C9.2, C10.2, C11.2, C12.2, C13.1, C14.2, C15.2, C17.2, D2.1 (K), D3.1 (K), D4.1 (K), IC1.2 (GND), IC1.13, J1.5 (GND), J2.6, J3.3, J3.5, J4.5, J5.5, J5.6, J6.6, J6.18, J7.2, J8.6, J8.17, J10.5, J10.6, J11.2, J12.4, J13.13, JP8.1 (A), R9.2, SW1.2, SW2.2, SW3.2, SW5.2, SW7.5, TP2.1, U1.1 (GND), U2.2 (GND), U3.3 (GND), U3.5 (GND), U3.21 (GND), U4.6 (GND), U4.18 (GND), U4.28 (GND), U4.39 (GND), U5.4 (CTS), U5.9 (GND), U6.JP1_5 (GND), U6.JP1_6 (GND), U6.JP6_2 (GND_1), U6.JP7_9 (GND_2), Y1.2, Y2.2
unnamed: BT1.1 (+), SW4.1
unnamed: C2.1, L1.1, Q1.2 (S), U2.1 (BATT), U2.3 (~SHDN)
unnamed: C4.1, JP2.1 (A), R12.2, U2.4 (OUT)
unnamed: C17.1, JP1.1 (A), R11.2, U1.2 (VO)
unnamed: D1.1 (K), JP8.2 (B)
unnamed: D1.2 (A), R5.2
unnamed: D2.2 (A), R4.2
unnamed: D3.2 (A), R18.2
unnamed: D4.2 (A), R10.2
unnamed: IC1.6 (GDO2), TP1.1
unnamed: IC1.7 (GDO0), JP7.2 (C)
unnamed: JP11.3 (B), U5.13 (VCCIO)
unnamed: L1.2, U2.5 (LX)
unnamed: Q1.1 (G), R9.1
unnamed: Q1.3 (D), SW4.2

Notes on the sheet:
BOBUINO-PINOUT
LED ROT
CC1101 Anschl. Standard PIN_OUT PIN 42 = GDO0 PIN 44 = CS PIN 1 = MOSI PIN 2 = MISO PIN 3 = SCK
LED GRÜN
Spannungsversorgung
Buchsenleiste für 1:1 PIN-Out
ARDUINO PRO MINI
1284P-AU
328P-AU
STECKADAPTER ARDUINO
STECKADAPTER AVR_CHIPS
BOARD 3.3V
FTDI 3.3V
CC1101
FTDI-Adapter und Arduino Pro Mini
ARDUINO AS ISP
CC1101 Frequenz-Test mit ARDUINO
ISPPROG ARDUINO
ARDUINO Vcc
ISP-DEAKTIV
ARDUINO PRO MINI AS ISP ISP PROG ARDUINO PRO MINI
ARDUINO PRO MINI AS ISP
Funktionswahl
Testsockel

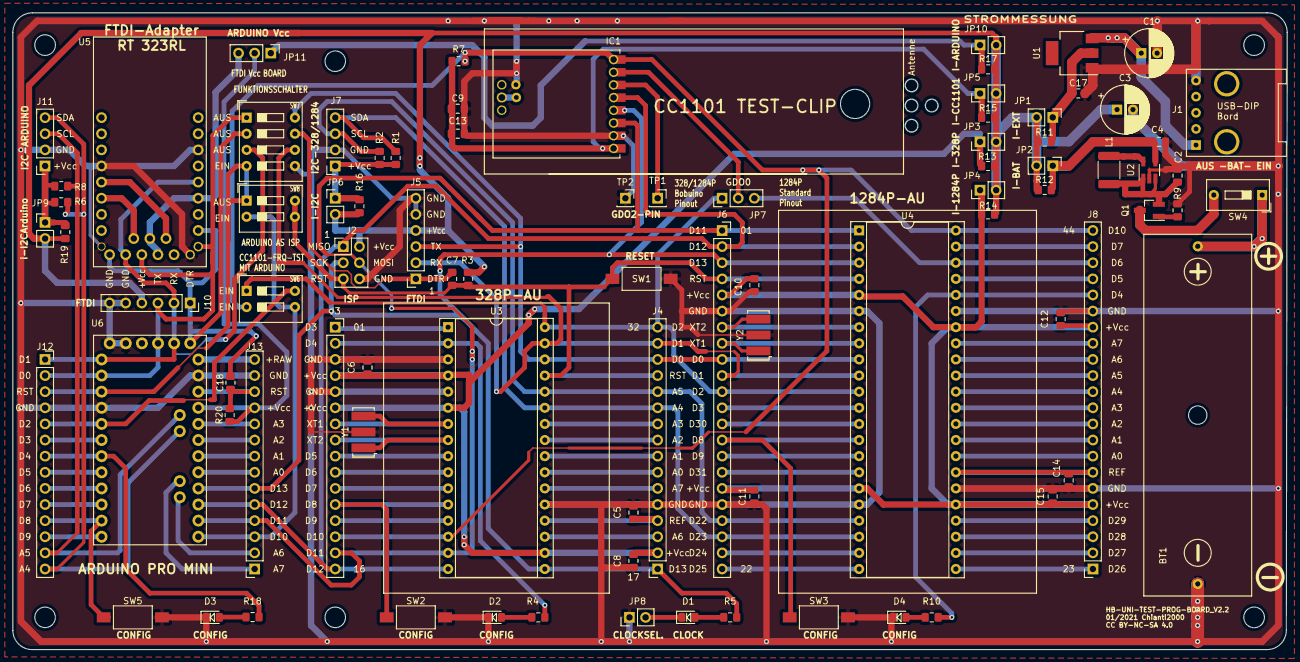
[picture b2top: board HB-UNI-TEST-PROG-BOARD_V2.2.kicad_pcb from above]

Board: 2 copper layers, 200.8 x 100.3 mm, 86 parts (0 on the bottom side), 101 nets.

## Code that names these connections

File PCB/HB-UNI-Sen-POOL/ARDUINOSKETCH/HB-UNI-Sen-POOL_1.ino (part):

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#define LCD_ROWS           4
#define LCD_COLUMNS        20

#define NTC_SENSE_PIN_1      A0 //PA0
#define NTC_SENSE_PIN_2      A1 //PA1
                                //PA2
                                //PA3
                                //PA4
#define PRESSURE_PIN         A5 //PA5
                                //PA6
#define ORPH_SIGNAL_PIN      A7 //PA7

#define LED_PIN              0  //PB0
#define CONFIG_BUTTON_PIN    1  //PB1
#define SC_1_PIN             2  //PB2
#define SC_2_PIN             3  //PB3
#define CC1101_CS_PIN        4  //PB4
                                //PB5...7 SPI

                                //PC0...1 I2C
#define SW_BUTTON_PIN_3      18 //PC2
#define SW_BUTTON_PIN_4      19 //PC3
#define RELAY_PIN_3          20 //PC4
#define RELAY_PIN_4          21 //PC5
#define RELAY_PIN_1          22 //PC6
#define RELAY_PIN_2          23 //PC7

                                //PD0...1 TX/RX FTDI
#define CC1101_GDO0           2 //PB2
#define SW_BUTTON_PIN_1      11 //PD3
#define SW_BUTTON_PIN_2      12 //PD4
                                //PD5
                                //PD6
#define SENSOR_SWITCH_PIN    15 //PD7
#define OFF LOW
#define ON  HIGH

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
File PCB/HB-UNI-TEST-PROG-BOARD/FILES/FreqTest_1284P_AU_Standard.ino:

//- -----------------------------------------------------------------------------------------------------------------------
// AskSin++
// 2016-10-31 papa Creative Commons - http://creativecommons.org/licenses/by-nc-sa/3.0/de/
// 2019-11-16 stan23 Creative Commons - http://creativecommons.org/licenses/by-nc-sa/3.0/de/
// ci-test=yes board=328p aes=no
//- -----------------------------------------------------------------------------------------------------------------------

// define this to read the device id, serial and device type from bootloader section
// #define USE_OTA_BOOTLOADER

#if defined ARDUINO_ARCH_STM32F1
  #define STORAGEDRIVER at24cX<0x50,128,32>
  #define TICKS_PER_SECOND 500UL
  #define USE_HW_SERIAL
 
  #include <SPI.h>    // when we include SPI.h - we can use LibSPI class
  #include <Wire.h>   // for I2C access to EEPROM
  #include <EEPROM.h> // the EEPROM library contains Flash Access Methods
#endif

#include <AskSinPP.h>
#include <Device.h>
#include <Register.h>


#if defined ARDUINO_ARCH_STM32F1
  // we use a BluePill
  #define CC1101_GDO0_PIN     PB0
  #define CC1101_CS_PIN       PA4
  // CC1101 communication uses HW-SPI
  #define LED_PIN             LED_BUILTIN
#else
  // we use a Pro Mini
  #define CC1101_GDO0_PIN     2    // PB2
  #define CC1101_CS_PIN       4    // PB4
  #define CC1101_MOSI_PIN     5    // PB5
  #define CC1101_MISO_PIN     6    // PB6
  #define CC1101_SCK_PIN      7    // PB7
  // Pro Mini LED
  #define LED_PIN             23    // PC7
#endif

// all library classes are placed in the namespace 'as'
using namespace as;

// define all device properties
const struct DeviceInfo PROGMEM devinfo = {
    {0x01,0x01,0x01},       // Device ID
    "FreqTest00",           // Device Serial
    {0x00,0x00},            // Device Model
    0x10,                   // Firmware Version
    as::DeviceType::Sensor, // Device Type
    {0x00,0x00}             // Info Bytes
};

/**
 * Configure the used hardware
 */
#if defined ARDUINO_ARCH_STM32F1
typedef LibSPI<CC1101_CS_PIN> RadioSPI;
#else
typedef AvrSPI<CC1101_CS_PIN, CC1101_MOSI_PIN, CC1101_MISO_PIN, CC1101_SCK_PIN> RadioSPI;
#endif
typedef Radio<RadioSPI, CC1101_GDO0_PIN> RadioType;
typedef StatusLed<LED_PIN> LedType;
typedef AskSin<LedType,NoBattery,RadioType> HalType;



#define STARTFREQ 0x656A             // frequency we start scanning
#define MINFREQ (STARTFREQ - 0x300)  // frequency we abort scanning
#define SEARCHSTEP 0x50              // step with during search
#define BOUNDSTEP 0x10               // step width during upper/lower bound analysis


// see https://github.com/AskSinPP/asksinpp.de/blob/master/Grundlagen/FAQ/Fehlerhafte_CC1101.md
// #define ACTIVE_PING
HMID PING_FROM(0x12,0x34,0x56);      // from address for status message e.g. switch
HMID PING_TO(0x99,0x66,0x99);        // to address for status message / central / CCU
#ifdef ACTIVE_PING
  #define SCANTIME seconds2ticks(5)  // maximal time to wait for a valid message
#else
  #define SCANTIME seconds2ticks(60) // maximal time to wait for a valid message
#endif



class TestDevice : public Device<HalType,DefList0>, Alarm {
  DefList0 l0;
  uint16_t freq, start, end;
  uint8_t received, rssi;
public:
  enum SearchMode { Search, Up, Down, Done };
  SearchMode mode;
  HMID id;

  typedef Device<HalType,DefList0> BaseDevice;
  TestDevice (const DeviceInfo& i,uint16_t addr) : BaseDevice(i,addr,l0,0), Alarm(0), l0(addr),
      freq(STARTFREQ), start(STARTFREQ), end(STARTFREQ),
      received(0), rssi(0), mode(Search)  {}
  virtual ~TestDevice () {}

  virtual void trigger (__attribute__ ((unused)) AlarmClock& clock) {
    DPRINT("  ");DDEC(received);
    if (!received) {
      DPRINTLN("");
    } else {
      DPRINT(" / -");DDEC(rssi);DPRINTLN("dBm");
    }

    if( mode == Search ) {
      if( received > 0 ) {
        start = end = freq;
        mode = Up; // start find upper bound
        DPRINTLN("Search for upper bound");
        setFreq(freq + BOUNDSTEP);
      }
      else {
        if( freq < MINFREQ ) mode = Done;
        if( freq <= STARTFREQ ) setFreq(STARTFREQ + (STARTFREQ-freq) + SEARCHSTEP);
        else setFreq(STARTFREQ - (freq-STARTFREQ));
      }
    }
    else if(mode == Up) {
      if( received > 0 ) {
        end = freq;
        setFreq(end + BOUNDSTEP);
      }
      else {
        mode = Down; // start find lower bound
        DPRINTLN("Search for lower bound");
        setFreq(start - BOUNDSTEP);
      }
    }
    else if(mode == Down) {
      if( received > 0 ) {
        start = freq;
        setFreq(start - BOUNDSTEP);
      }
      else {
        mode = Done;
      }
    }
    if( mode == Done ) {
      DPRINT("\nDone: 0x21");DHEX(start);DPRINT(" - 0x21");DHEXLN(end);
      if( start == end && start == STARTFREQ ) {
        DPRINT("Could not receive any message");
      }
      else {
        freq = start+((end - start)/2);
        DPRINT("Calculated Freq: 0x21");DHEX((uint8_t)(freq>>8));DHEX((uint8_t)(freq&0xff));
        printFreq(0x210000 + freq);DPRINTLN("");

        // store frequency
        DPRINT("Store into config area: ");DHEX((uint8_t)(freq>>8));DHEX((uint8_t)(freq&0xff));
        StorageConfig sc = getConfigArea();
#if defined ARDUINO_ARCH_STM32F1
        Wire.begin();
        DPRINT(".");
#endif
        sc.clear();
        DPRINT(".");
        sc.setByte(CONFIG_FREQ1, freq>>8);
        DPRINT(".");
        sc.setByte(CONFIG_FREQ2, freq&0xff);
        DPRINT(".");
        sc.validate();

        DPRINTLN("stored!");
#if defined ARDUINO_ARCH_STM32F1
        // measurement is done, loop here forever
        while(1);
#else
        activity().savePower<Sleep<> >(this->getHal());
#endif
      }
    }
  }

  virtual bool process(Message& msg) {
    msg.from().dump(); DPRINT(".");
    rssi = max(rssi,radio().rssi());
    received++;
    if( received > 0 ) {
      trigger(sysclock);
    }
    return true;
  }

  bool init (HalType& hal) {
    this->setHal(hal);
    this->getDeviceID(id);
    hal.init(id);

    DPRINTLN("Start searching ...");
    setFreq(STARTFREQ);
    return false;
  }

  void setFreq (uint16_t current) {
    sysclock.cancel(*this);
    freq = current;
    rssi=0;
    received=0;
    DPRINT("Freq 0x21");DHEX(freq);
    printFreq(0x210000 + freq);
    DPRINT(": ");
    this->radio().initReg(CC1101_FREQ2, 0x21);
    this->radio().initReg(CC1101_FREQ1, freq >> 8);
    this->radio().initReg(CC1101_FREQ0, freq & 0xff);
    set(SCANTIME);
    sysclock.add(*this);
  }

  void printFreq(uint32_t freq) {
    char buffer[16];
    float val = (float)freq * 26.0 / 65536.0;
    dtostrf(val, 8, 3, buffer);
    DPRINT(buffer);DPRINT(" MHz");
  }
};

HalType hal;
TestDevice sdev(devinfo,0x20);

class InfoSender : public Alarm {
  class channel {
  public:
    uint8_t number() const {return 1; }
    uint8_t status() const {return 0; }
    uint8_t flags()  const {return 0; }
    void patchStatus(__attribute__ ((unused)) Message& msg) {}
    void changed(__attribute__ ((unused)) bool b) {}
  };
  uint8_t cnt;
  channel ch;
public:
  InfoSender () : Alarm(0), cnt(0) {}
  virtual ~InfoSender () {}

  virtual void trigger (AlarmClock& clock) {
#ifdef ACTIVE_PING
    InfoActuatorStatusMsg msg;
    msg.init(cnt++, ch, hal.radio.rssi());
    msg.to(PING_TO);
    msg.from(PING_FROM);
    msg.ackRequired();
    msg.setRpten();
    sdev.radio().write(msg,msg.burstRequired());
#endif
    sdev.led().ledOn(millis2ticks(100), 0);
    if( sdev.mode != TestDevice::SearchMode::Done ) {
      set(seconds2ticks(1));
      clock.add(*this);
    }
  }
} info;

void setup () {
#if defined ARDUINO_ARCH_STM32F1
  delay(5000);
#endif
  DINIT(57600,ASKSIN_PLUS_PLUS_IDENTIFIER);
  sdev.init(hal);
  // start sender
  info.trigger(sysclock);
}

void loop() {
  sdev.pollRadio();
  hal.runready();
}

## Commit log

2021-02-19 Create HB-UNI-TEST-PROG-BOARD
2021-02-19 Create GERBER
2021-02-19 Create STL
2021-02-19 Create Bild
2021-02-19 Create Test
2021-09-16 Add Arduino-as-ISP Sketch and Docu
2021-09-17 Update README.md
    geändert Elkos 16V -> mind. 5V
2023-05-08 Create HB-UNI-Sen-POOL
2023-05-08 Create KiCAD
2023-05-08 Create Schema
2023-05-08 Create y
2023-05-08 Create x

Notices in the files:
PCB/HB-UNI-Sen-POOL/ARDUINOSKETCH/HB-UNI-Sen-POOL_1.ino:
2021-03-03 jp112sdl Creative Commons - http://creativecommons.org/licenses/by-nc-sa/3.0/de
PCB/HB-UNI-Sen-POOL/KiCAD/HB-UNI-SEN-POOL_2023_05.1.kicad_pcb:
CC BY-NC-SA 4.0
PCB/HB-UNI-TEST-PROG-BOARD/README.md:
Creative Commons BY-NC-SA
Creative Commons License
This work is licensed under a [Creative Commons Attribution-NonCommercial-ShareAlike 4.0 International License](http://creativecommons.org/licenses/by-nc-sa/4.0/).
